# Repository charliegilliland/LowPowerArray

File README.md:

# LowPowerArray

This repository contains the hardware design files and firmware for a low-power acoustic array.
Up to 8 channels of microphone data are sampled at 48kHz and saved to an SD card.
Data acquisition is synchronized to UTC time with a GPS.

## Theory of Operation

### Power
The LowPowerArray can be powered via USB or pin headers on J101.
The power source is selected by placement of a jumper on J101.
A servo-style connector can be plugged into J101.
Refer to the schematics in [HardwareDesign](HardwareDesign/LowPowerArray/) for pin descriptions.

### Modes
There are two modes of operation: Manual and Automatic.
The mode is selected with a jumper on J201.

In Manual mode (jumper present) data acquisition is started and stopped using the pushbutton connected to J202.

In Automatic mode (jumper not present) data acquisition will begin automatically once power is applied and the GPS is locked.
If the button is pressed while in Automatic mode, the data acquisition will be stopped and the device will revert to Manual mode.

### Status
At startup, the device will wait for a GPS lock, unless ```GPS_WAIT_LOCK``` is defined as 0 (useful for lab testing).
When the GPS is locked, the LED will quickly illuminate several times, indicating that it is ready to start data acquisition.

While the data acquisition is running, the LED will illuminate every other second.

Status messages will be printed over the UART pins on J201, and also over USB via the virtual COM port.

### Programming
The STM32 microcontroller is programmed via SWD using the pins SWDIO, SWCLK, NRST on J201.
A Nucleo development board, or dedicated programmer, can be used to program the device.

### Microphone Connections
The 10-pin FFC connector, J1, is used to connect to a microphone board.

Alternatively, the BCLK, FSYNC, and DATA pins are available as pin headers on J201.

### SD Card Storage
Audio and GPS data are stored on the microSD card.
The card must be formatted as exFAT.

At startup, the device will create a new directory with the prefix ```filesXXXX```, where XXXX is a number: i.e. ```files0001```.

Audio and GPS files will be stored in the newly created directory, with file names ```audioXXXX.pcm``` and ```gpsXXXX.txt```.
Audio data is raw PCM format, with 8 channels and 32-bit word length.
GPS data is stored as plain text NMEA sentences, exactly as it is received from the GPS module.

GPS data can be tied to the audio data by matching the file numbers.
There is one pair of GPS messages for each second, where the first pair of GPS messages is tied to the first frame of audio in the audio file.

### GPS Module
The GPS module provides the PPS (pulse per second) and BCLK (bit clock) signals, as well as location and time via NMEA messages over UART.

Be sure to program the GPS module using the configuration file ```charlie-m8t-lowpower.txt```.

There is a battery connector, labeled BT101, which can provide backup power to the GPS.
The battery should be a 3v coin-cell or equivalent, and are commonly available as CMOS batteries.

Be sure to plug in the battery with the correct polarity (+ and - are marked on the v2 board).

If for some reason the GPS is not used, an auxiliary clock source can be used by populating a 12.288MHz crystal oscillator X501.
If this is used, select the clock source by placing R502 instead of R501.
Using the auxiliary clock source will require firmware changes to account for the missing PPS signal, and no GPS messages.
At time of writing this is not supported by the firmware.

For debugging purposes, when GPS lock is not required to start data acquisition, go to the file ```gps_mgr.h``` and change ```GPS_WAIT_LOCK``` to 0,
and re-program the device.
This will allow you to test the device in the lab, where GPS signals are not available.

## Programming Guide

### main.c
The file [main.c](Firmware/Core/Src/main.c) mostly contains code generated by CubeIDE. This file simply initializes the peripherals, and calls the user_app_init and user_app_loop functions.
This file should not have to be changed.

### user_app.c
The file [user_app.c](Firmware/Core/Src/user_app.c) contains the high-level runtime behavior of the device.
This includes the main endless while loop, the data acquisition loop, and button and PPS callback functions.

The endless while loop in user_app_loop implements the state diagram described below.

### aud_mgr.h
The file [aud_mgr.h](Firmware/Core/Inc/aud_mgr.h) contains the audio-specific code.
This uses the SAI peripheral in DMA mode, so that audio data can be received 'in the background' while the CPU is working on other tasks.

The ```HAL_SAI_RxCpltCallback``` is called by the hardware when a buffer of new data is ready.
In this function, the DMA buffer pointer is changed to the next buffer in the ring buffer.
The ring buffer allows for multiple buffers to be stored before they are written to the SD card. 

If there is an SAI error, or ring buffer overflow, the data acquisition will be stopped and the PPS will be re-synchronized.

### sd_mgr.h
The file [sd_mgr.h](Firmware/Core/Inc/sd_mgr.h) contains the sd card-specific code.
This code contains functions for starting new files, and writing to existing files.

### gps_mgr.h
The file [gps_mgr.h](Firmware/Core/Inc/gps_mgr.h) contains the GPS-specific code.
GPS data is received over USART2 in DMA mode.

When the GPS messages have been received, the ```HAL_UARTEx_RxEventCallback``` function will be called by the hardware.
The received messages will be copied to local buffers, and the RX will be restarted to handle the next message.

### inline functions
Many of the functions implemented in the peripheral files are ```inline``` functions.
This is done for execution speed: basically instead of actually calling those functions,
the compiler will copy that code to where the function was called.

### DAQ State Diagram
This figure describes the various states that the device can be in, and the events that cause a state change.
The ```daq_stat``` variable declared in user_app.c is used to read and change state in the code.

## Future Work

### Directory / file naming
It would probably be better to name the files using the UTC date and time as received from the GPS.
This would require parsing each GPS message, and some more logic for dealing with the timing in creating the files.

### Control and monitoring over UART / USB
It might be possible to start and stop the data acquisition over UART or USB, though I haven't explored this in detail.
This would allow a remote computer, such as a raspberry pi, to control the data acquisition.
Additionally, a telemetry radio could be connected to the UART serial port for remote status monitoring and control.

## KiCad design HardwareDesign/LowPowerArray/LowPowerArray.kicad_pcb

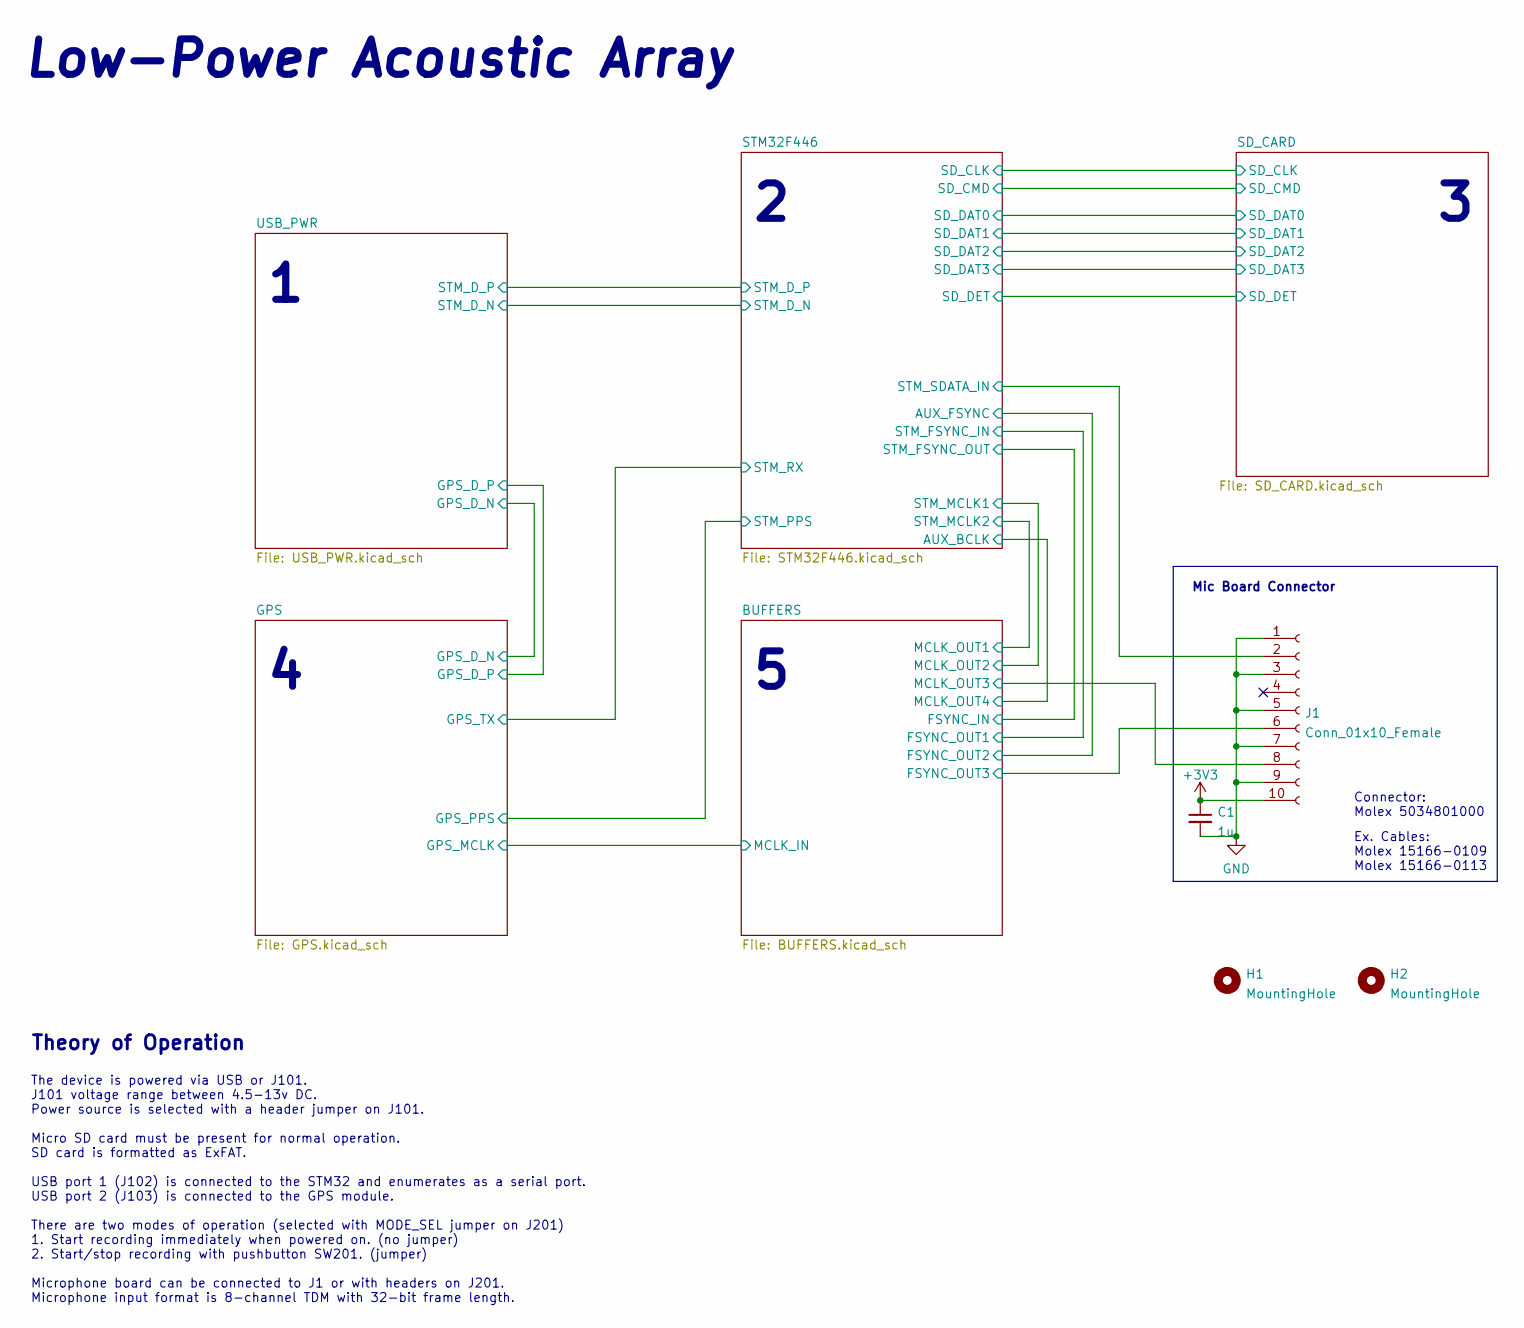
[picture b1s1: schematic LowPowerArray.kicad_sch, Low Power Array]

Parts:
C1: 1u; C_0402_1005Metric
H1, H2: MountingHole; MountingHole_3.2mm_M3
J1: Conn_01x10_Female; MOLEX_5034801000

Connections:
+3V3: C1.1, J1.10; also elsewhere on the board
/BUFFERS/FSYNC_OUT3: J1.6; also elsewhere on the board
/BUFFERS/MCLK_OUT3: J1.8; also elsewhere on the board
/STM32F446/STM_SDATA_IN: J1.2; also elsewhere on the board
GND: C1.2, J1.1, J1.3, J1.5, J1.7, J1.9; also elsewhere on the board

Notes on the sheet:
The device is powered via USB or J101. J101 voltage range between 4.5-13v DC. Power source is selected with a header jumper on J101. Micro SD card must be present for normal operation. SD card is formatted as ExFAT. USB port 1 (J102) is connected to the STM32 and enumerates as a serial port. USB po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
Connector: Molex 5034801000
Theory of Operation
Mic Board Connector
Low-Power Acoustic Array
Ex. Cables: Molex 15166-0109 Molex 15166-0113

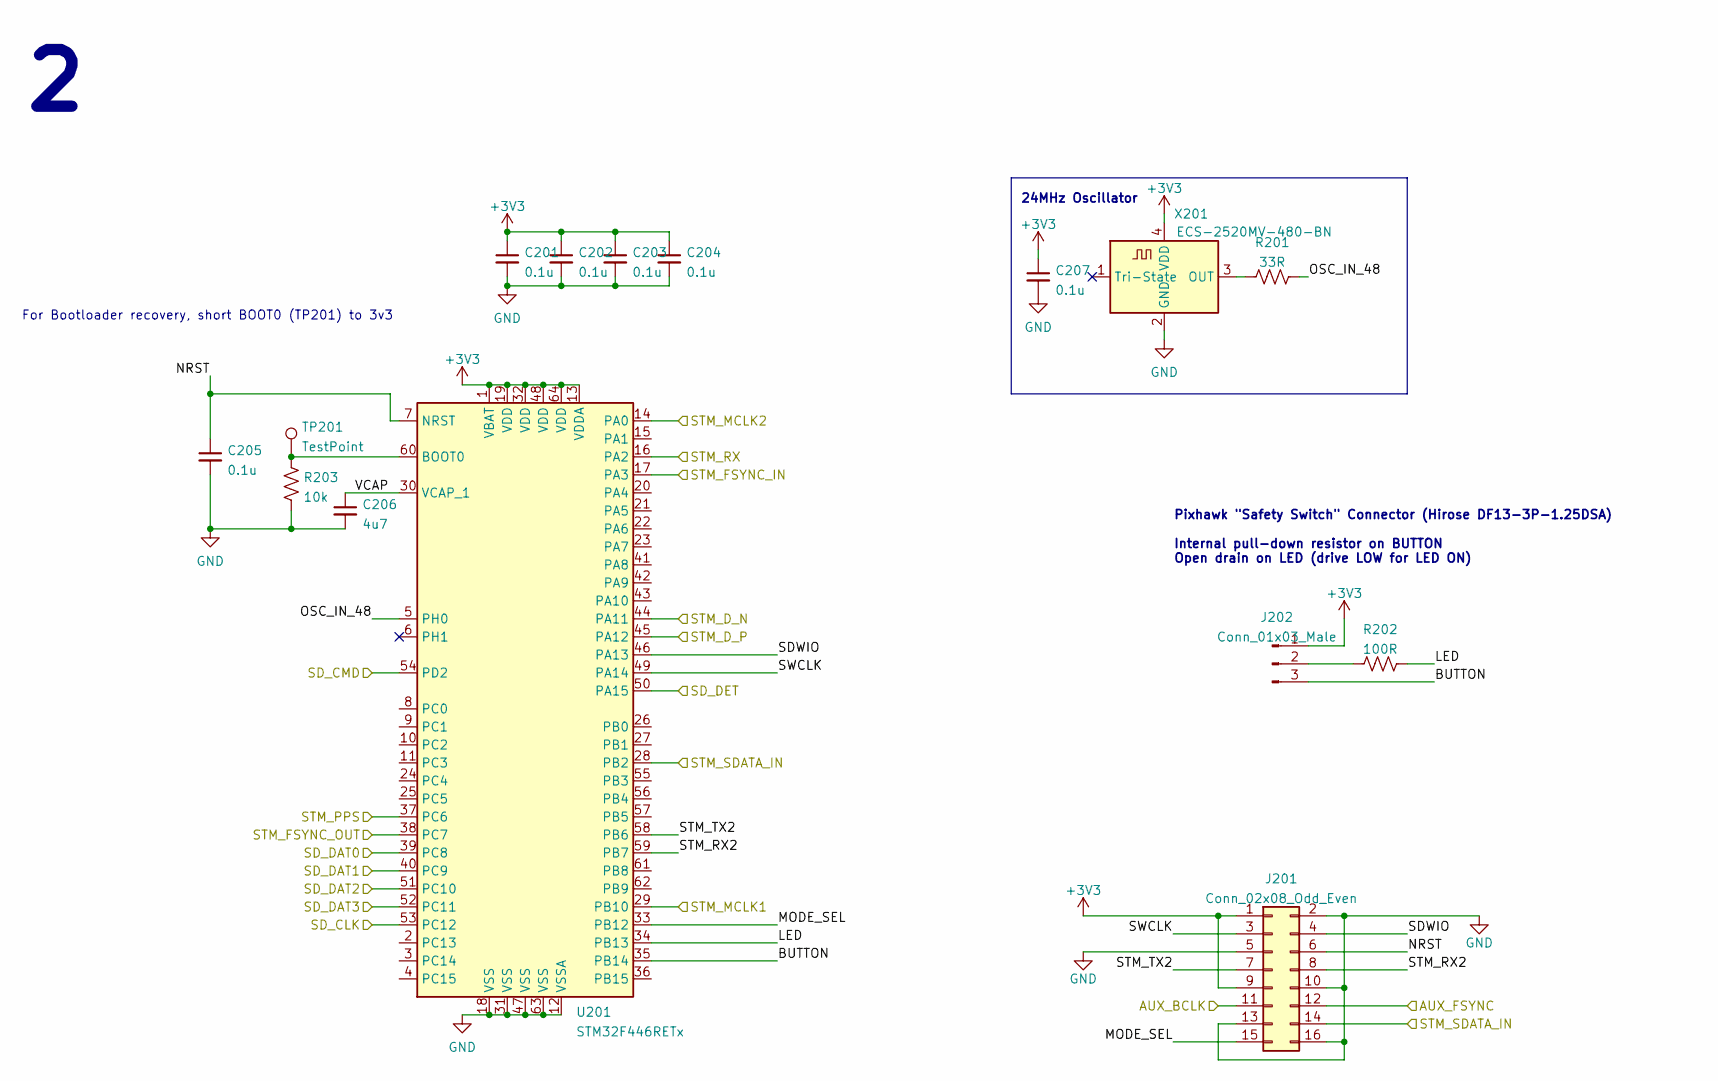
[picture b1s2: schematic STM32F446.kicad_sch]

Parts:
C201, C202, C203, C204, C205, C207: 0.1u; C_0402_1005Metric
C206: 4u7; C_0402_1005Metric
J201: Conn_02x08_Odd_Even; PinHeader_2x08_P2.54mm_Vertical_SMD
J202: Conn_01x03_Male; Hirose_DF13-03P-1.25DSA_1x03_P1.25mm_Vertical
R201: 33R; R_0402_1005Metric
R202: 100R; R_0402_1005Metric
R203: 10k; R_0402_1005Metric
TP201: TestPoint; TestPoint_Pad_D1.5mm
U201: STM32F446RETx; LQFP-64_10x10mm_P0.5mm
X201: ECS-2520MV-480-BN; Oscillator_SMD_ECS_2520MV-xxx-xx-4Pin_2.5x2.0mm

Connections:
+3V3: C201.1, C202.1, C203.1, C204.1, C207.1, J201.1, J201.9, J202.1, U201.1 (VBAT), U201.13 (VDDA), U201.19 (VDD), U201.32 (VDD), U201.48 (VDD), U201.64 (VDD), X201.4 (VDD); also elsewhere on the board
/BUFFERS/FSYNC_IN: U201.38 (PC7); also elsewhere on the board
/BUFFERS/FSYNC_OUT1: U201.17 (PA3); also elsewhere on the board
/BUFFERS/FSYNC_OUT2: J201.12; also elsewhere on the board
/BUFFERS/MCLK_OUT1: U201.14 (PA0); also elsewhere on the board
/BUFFERS/MCLK_OUT2: U201.29 (PB10); also elsewhere on the board
/BUFFERS/MCLK_OUT4: J201.11; also elsewhere on the board
/GPS/GPS_PPS: U201.37 (PC6); also elsewhere on the board
/GPS/GPS_TX: U201.16 (PA2); also elsewhere on the board
/SD_CARD/SD_CLK: U201.53 (PC12); also elsewhere on the board
/SD_CARD/SD_CMD: U201.54 (PD2); also elsewhere on the board
/SD_CARD/SD_DAT0: U201.39 (PC8); also elsewhere on the board
/SD_CARD/SD_DAT1: U201.40 (PC9); also elsewhere on the board
/SD_CARD/SD_DAT2: U201.51 (PC10); also elsewhere on the board
/SD_CARD/SD_DAT3: U201.52 (PC11); also elsewhere on the board
/SD_CARD/SD_DET: U201.50 (PA15); also elsewhere on the board
/STM32F446/BUTTON: J202.3, U201.35 (PB14)
/STM32F446/LED: R202.2, U201.34 (PB13)
/STM32F446/MODE_SEL: J201.15, U201.33 (PB12)
/STM32F446/NRST: C205.1, J201.6, U201.7 (NRST)
/STM32F446/OSC_IN_48: R201.2, U201.5 (PH0)
/STM32F446/SDWIO: J201.4, U201.46 (PA13)
/STM32F446/STM_D_N: U201.44 (PA11); also elsewhere on the board
/STM32F446/STM_D_P: U201.45 (PA12); also elsewhere on the board
/STM32F446/STM_RX2: J201.8, U201.59 (PB7)
/STM32F446/STM_SDATA_IN: J201.14, U201.28 (PB2); also elsewhere on the board
/STM32F446/STM_TX2: J201.7, U201.58 (PB6)
/STM32F446/SWCLK: J201.3, U201.49 (PA14)
/STM32F446/VCAP: C206.1, U201.30 (VCAP_1)
GND: C201.2, C202.2, C203.2, C204.2, C205.2, C206.2, C207.2, J201.2, J201.5, J201.10, J201.13, J201.16, R203.1, U201.12 (VSSA), U201.18 (VSS), U201.31 (VSS), U201.47 (VSS), U201.63 (VSS), X201.2 (GND); also elsewhere on the board
unnamed: J202.2, R202.1
unnamed: R201.1, X201.3 (OUT)
unnamed: R203.2, TP201.1, U201.60 (BOOT0)

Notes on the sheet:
24MHz Oscillator
For Bootloader recovery, short BOOT0 (TP201) to 3v3
Pixhawk "Safety Switch" Connector (Hirose DF13-3P-1.25DSA) Internal pull-down resistor on BUTTON Open drain on LED (drive LOW for LED ON)

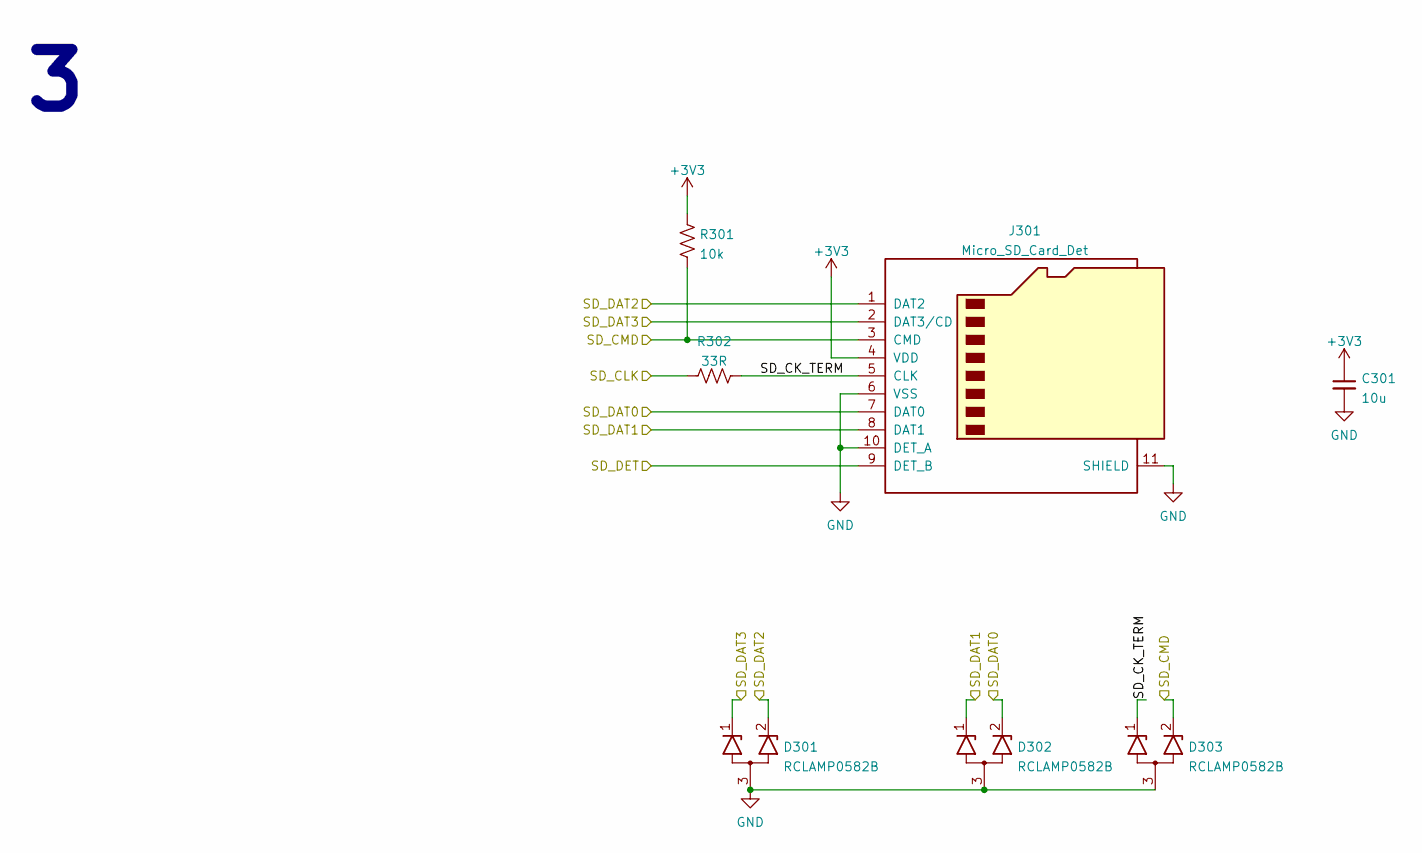
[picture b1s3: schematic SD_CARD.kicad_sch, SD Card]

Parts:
C301: 10u; C_0805_2012Metric
D301, D302, D303: RCLAMP0582B; SOT-416
J301: Micro_SD_Card_Det; microSD_HC_Molex_104031-0811
R301: 10k; R_0402_1005Metric
R302: 33R; R_0402_1005Metric

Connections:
+3V3: C301.1, J301.4 (VDD), R301.1; also elsewhere on the board
/SD_CARD/SD_CK_TERM: D303.1 (K1), J301.5 (CLK), R302.2
/SD_CARD/SD_CLK: R302.1; also elsewhere on the board
/SD_CARD/SD_CMD: D303.2 (K2), J301.3 (CMD), R301.2; also elsewhere on the board
/SD_CARD/SD_DAT0: D302.2 (K2), J301.7 (DAT0); also elsewhere on the board
/SD_CARD/SD_DAT1: D302.1 (K1), J301.8 (DAT1); also elsewhere on the board
/SD_CARD/SD_DAT2: D301.2 (K2), J301.1 (DAT2); also elsewhere on the board
/SD_CARD/SD_DAT3: D301.1 (K1), J301.2 (DAT3/CD); also elsewhere on the board
/SD_CARD/SD_DET: J301.9 (DET_B); also elsewhere on the board
GND: C301.2, D301.3 (A), D302.3 (A), D303.3 (A), J301.6 (VSS), J301.10 (DET_A), J301.11 (SHIELD); also elsewhere on the board

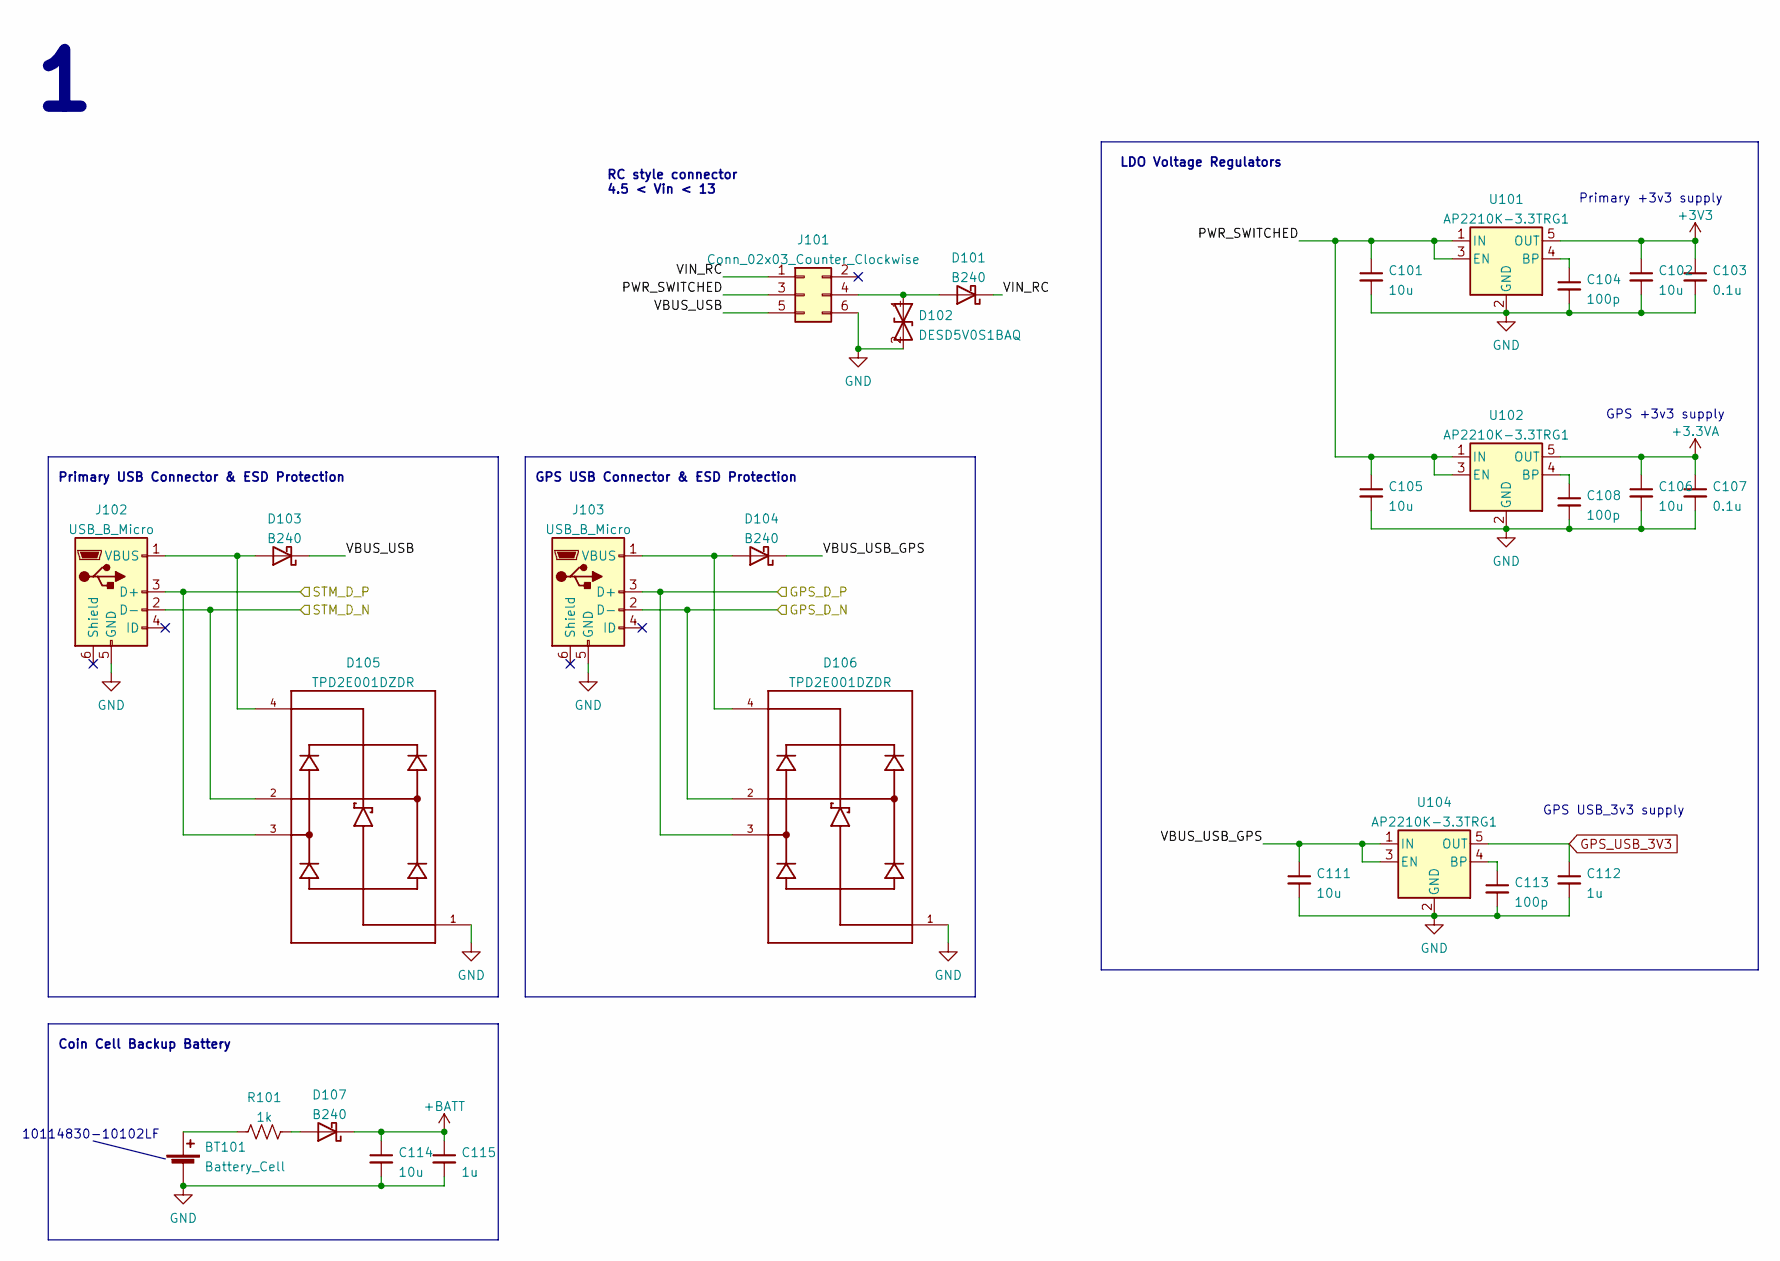
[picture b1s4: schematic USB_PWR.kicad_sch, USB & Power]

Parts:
BT101: Battery_Cell; Amphenol_10114830-10102LF
C101, C102, C105, C106, C111, C114: 10u; C_0805_2012Metric
C103, C107: 0.1u; C_0402_1005Metric
C104, C108, C113: 100p; C_0402_1005Metric
C112, C115: 1u; C_0402_1005Metric
D101, D103, D104, D107: B240; D_SMB
D102: DESD5V0S1BAQ; D_SOD-323
D105, D106: TPD2E001DZDR; SOT192P237X122-4N; PARTREV I
J101: Conn_02x03_Counter_Clockwise; PinHeader_2x03_P2.54mm_Vertical
J102, J103: USB_B_Micro; USB_Micro-B_Molex_47346-0001
R101: 1k; R_0402_1005Metric
U101, U102, U104: AP2210K-3.3TRG1; SOT-23-5

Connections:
+3.3VA: C106.1, C107.1, U102.5 (OUT); also elsewhere on the board
+3V3: C102.1, C103.1, U101.5 (OUT); also elsewhere on the board
+BATT: C114.1, C115.1, D107.1 (K); also elsewhere on the board
/GPS/GPS_D_N: D106.2, J103.2 (D-); also elsewhere on the board
/GPS/GPS_D_P: D106.3, J103.3 (D+); also elsewhere on the board
/STM32F446/STM_D_N: D105.2, J102.2 (D-); also elsewhere on the board
/STM32F446/STM_D_P: D105.3, J102.3 (D+); also elsewhere on the board
/USB_PWR/PWR_SWITCHED: C101.1, C105.1, J101.3, U101.1 (IN), U101.3 (EN), U102.1 (IN), U102.3 (EN)
/USB_PWR/VBUS_USB: D103.1 (K), J101.5
/USB_PWR/VBUS_USB_GPS: C111.1, D104.1 (K), U104.1 (IN), U104.3 (EN)
/USB_PWR/VIN_RC: D101.1 (K), J101.1
GND: BT101.2 (-), C101.2, C102.2, C103.2, C104.2, C105.2, C106.2, C107.2, C108.2, C111.2, C112.2, C113.2, C114.2, C115.2, D102.2 (A2), D105.1, D106.1, J101.6, J102.5 (GND), J103.5 (GND), U101.2 (GND), U102.2 (GND), U104.2 (GND); also elsewhere on the board
GPS_USB_3V3: C112.1, U104.5 (OUT); also elsewhere on the board
unnamed: BT101.1 (+), R101.1
unnamed: C104.1, U101.4 (BP)
unnamed: C108.1, U102.4 (BP)
unnamed: C113.1, U104.4 (BP)
unnamed: D101.2 (A), D102.1 (A1), J101.4
unnamed: D103.2 (A), D105.4, J102.1 (VBUS)
unnamed: D104.2 (A), D106.4, J103.1 (VBUS)
unnamed: D107.2 (A), R101.2

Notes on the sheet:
GPS USB Connector & ESD Protection
RC style connector 4.5 < Vin < 13
GPS +3v3 supply
Coin Cell Backup Battery
GPS USB_3v3 supply
Primary USB Connector & ESD Protection
LDO Voltage Regulators
Primary +3v3 supply
10114830-10102LF

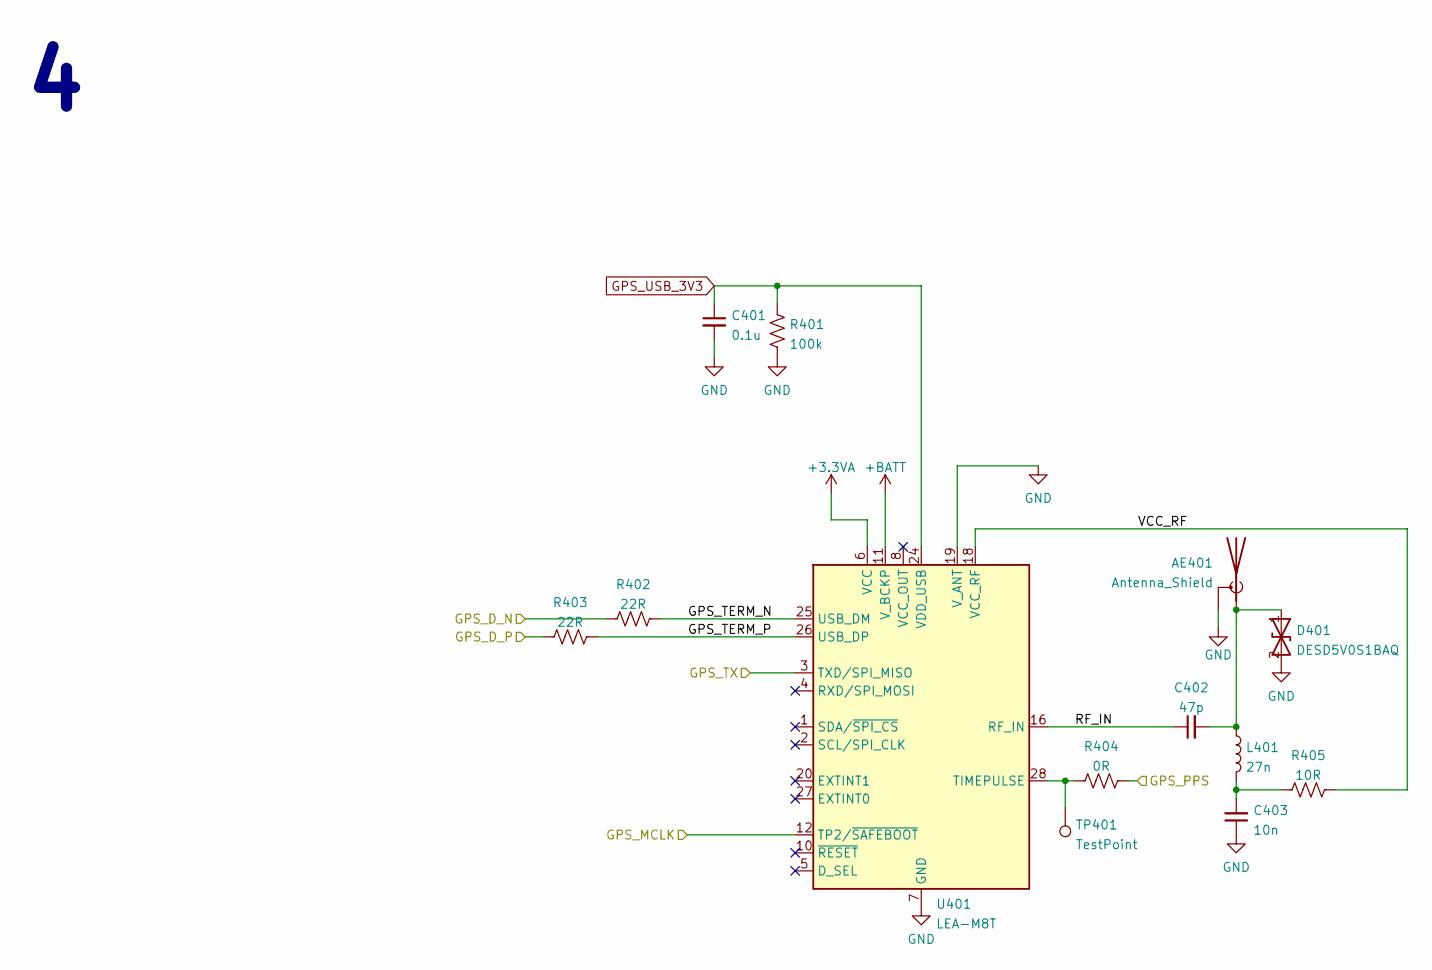
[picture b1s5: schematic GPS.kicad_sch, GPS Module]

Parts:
AE401: Antenna_Shield; U.FL_Hirose_U.FL-R-SMT-1_Vertical
C401: 0.1u; C_0402_1005Metric
C402: 47p; C_0402_1005Metric
C403: 10n; C_0402_1005Metric
D401: DESD5V0S1BAQ; D_SOD-323
L401: 27n; L_0402_1005Metric
R401: 100k; R_0402_1005Metric
R402, R403: 22R; R_0402_1005Metric
R404: 0R; R_0402_1005Metric
R405: 10R; R_0402_1005Metric
TP401: TestPoint; TestPoint_Pad_D1.5mm
U401: LEA-M8T; ublox_LEA

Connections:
+3.3VA: U401.6 (VCC); also elsewhere on the board
+BATT: U401.11 (V_BCKP); also elsewhere on the board
/BUFFERS/MCLK_IN: U401.12 (TP2/~SAFEBOOT); also elsewhere on the board
/GPS/GPS_D_N: R402.1; also elsewhere on the board
/GPS/GPS_D_P: R403.1; also elsewhere on the board
/GPS/GPS_PPS: R404.2; also elsewhere on the board
/GPS/GPS_TERM_N: R402.2, U401.25 (USB_DM)
/GPS/GPS_TERM_P: R403.2, U401.26 (USB_DP)
/GPS/GPS_TX: U401.3 (TXD/SPI_MISO); also elsewhere on the board
/GPS/RF_IN: C402.1, U401.16 (RF_IN)
/GPS/VCC_RF: R405.2, U401.18 (VCC_RF)
GND: AE401.2 (Shield), C401.2, C403.1, D401.2 (A2), R401.1, U401.7 (GND), U401.13 (GND), U401.14 (GND), U401.15 (GND), U401.17 (GND), U401.19 (V_ANT); also elsewhere on the board
GPS_USB_3V3: C401.1, R401.2, U401.24 (VDD_USB); also elsewhere on the board
unnamed: AE401.1 (A), C402.2, D401.1 (A1), L401.1
unnamed: C403.2, L401.2, R405.1
unnamed: R404.1, TP401.1, U401.28 (TIMEPULSE)

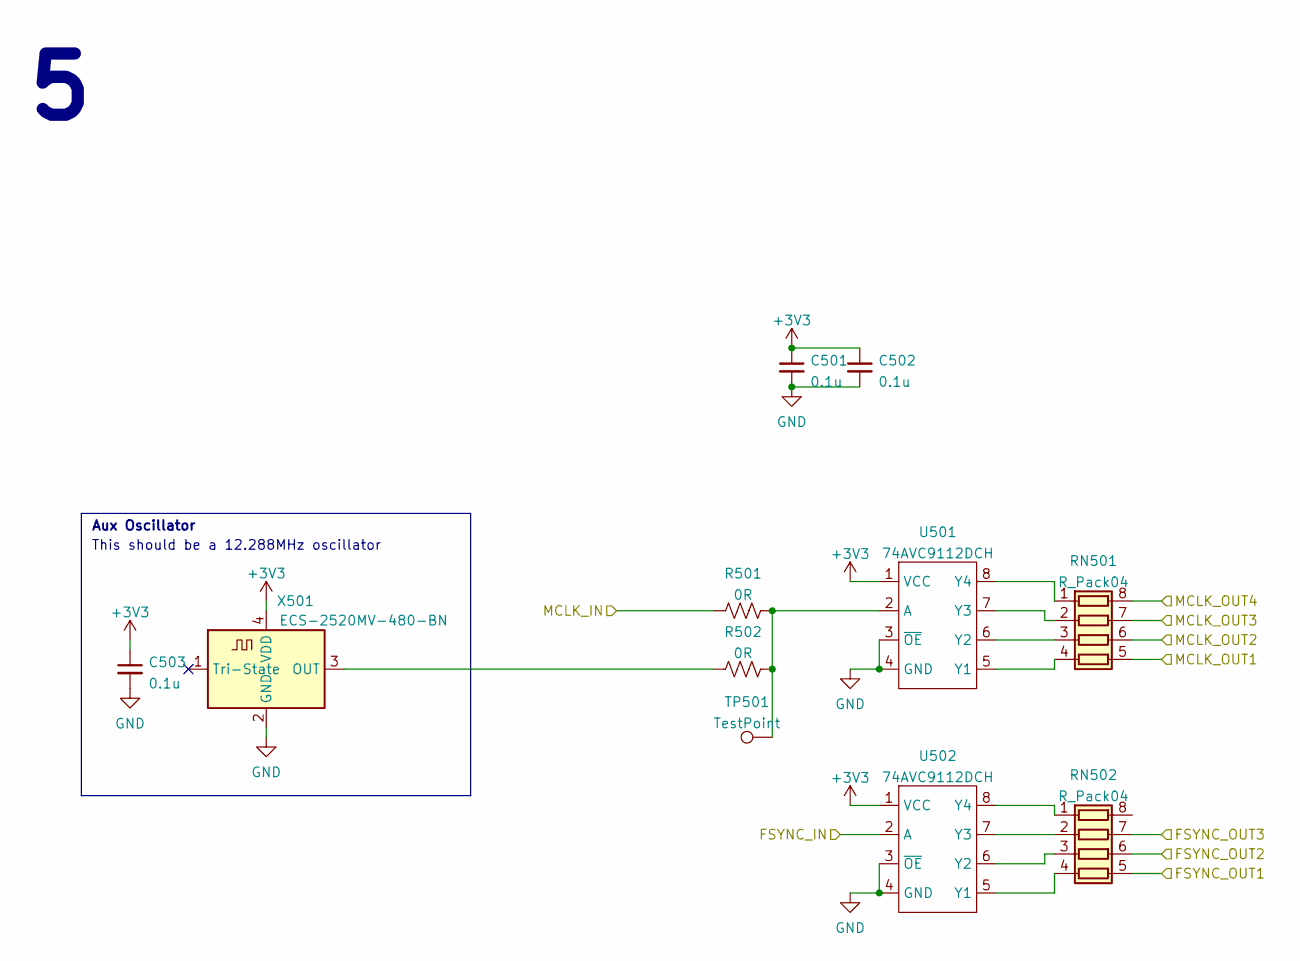
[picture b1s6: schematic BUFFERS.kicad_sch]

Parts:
C501, C502, C503: 0.1u; C_0402_1005Metric
R501, R502: 0R; R_0402_1005Metric
RN501, RN502: R_Pack04; R_Array_Concave_4x0402
TP501: TestPoint; TestPoint_Pad_D1.5mm
U501, U502: 74AVC9112DCH; VSSOP-8_2.3x2mm_P0.5mm
X501: ECS-2520MV-480-BN; Oscillator_SMD_ECS_2520MV-xxx-xx-4Pin_2.5x2.0mm

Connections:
+3V3: C501.1, C502.1, C503.1, U501.1 (VCC), U502.1 (VCC), X501.4 (VDD); also elsewhere on the board
/BUFFERS/FSYNC_IN: U502.2 (A); also elsewhere on the board
/BUFFERS/FSYNC_OUT1: RN502.5 (R4.2); also elsewhere on the board
/BUFFERS/FSYNC_OUT2: RN502.6 (R3.2); also elsewhere on the board
/BUFFERS/FSYNC_OUT3: RN502.7 (R2.2); also elsewhere on the board
/BUFFERS/MCLK_IN: R501.1; also elsewhere on the board
/BUFFERS/MCLK_OUT1: RN501.5 (R4.2); also elsewhere on the board
/BUFFERS/MCLK_OUT2: RN501.6 (R3.2); also elsewhere on the board
/BUFFERS/MCLK_OUT3: RN501.7 (R2.2); also elsewhere on the board
/BUFFERS/MCLK_OUT4: RN501.8 (R1.2); also elsewhere on the board
GND: C501.2, C502.2, C503.2, U501.3 (~OE), U501.4 (GND), U502.3 (~OE), U502.4 (GND), X501.2 (GND); also elsewhere on the board
unnamed: R501.2, R502.2, TP501.1, U501.2 (A)
unnamed: R502.1, X501.3 (OUT)
unnamed: RN501.1 (R1.1), U501.8 (Y4)
unnamed: RN501.2 (R2.1), U501.7 (Y3)
unnamed: RN501.3 (R3.1), U501.6 (Y2)
unnamed: RN501.4 (R4.1), U501.5 (Y1)
unnamed: RN502.1 (R1.1), U502.8 (Y4)
unnamed: RN502.2 (R2.1), U502.7 (Y3)
unnamed: RN502.3 (R3.1), U502.6 (Y2)
unnamed: RN502.4 (R4.1), U502.5 (Y1)

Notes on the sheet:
This should be a 12.288MHz oscillator
Aux Oscillator

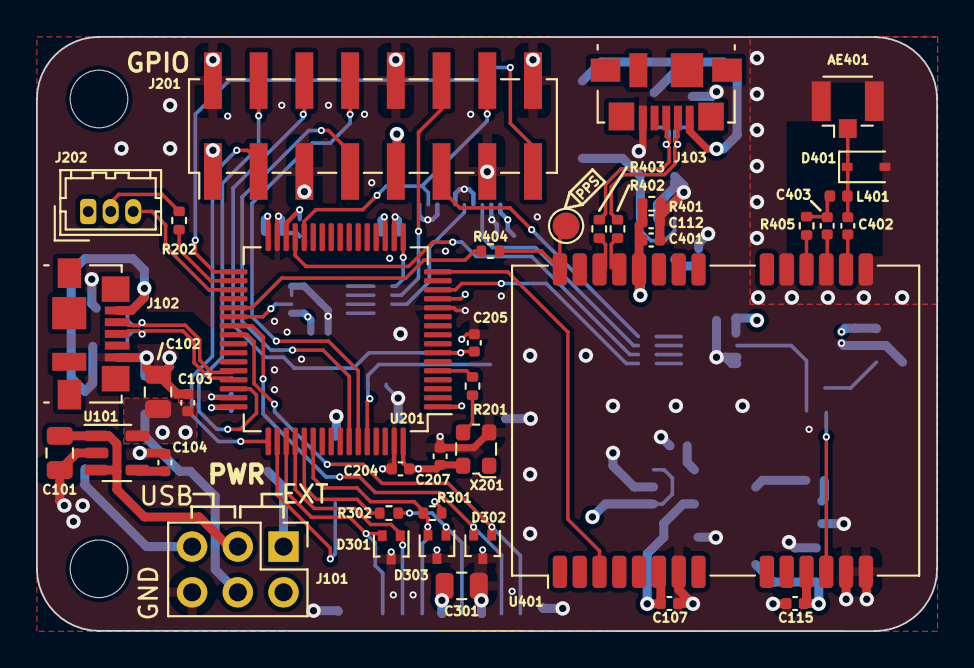
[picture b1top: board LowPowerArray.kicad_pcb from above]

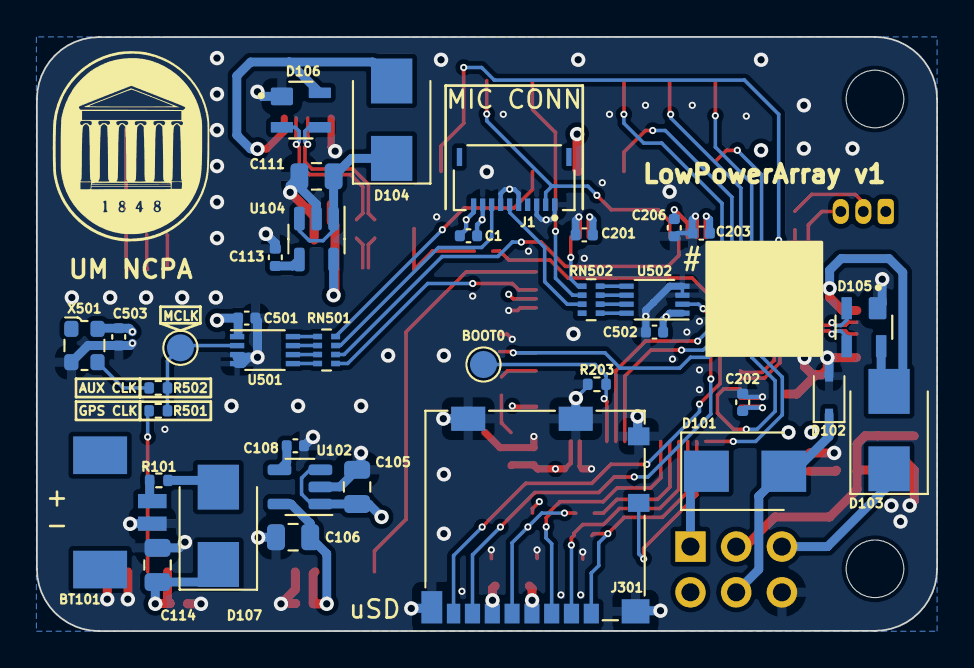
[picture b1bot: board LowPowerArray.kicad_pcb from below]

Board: 6 copper layers, 50.0 x 33.0 mm, 78 parts (37 on the bottom side), 71 nets.

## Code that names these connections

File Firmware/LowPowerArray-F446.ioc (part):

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Mcu.Name=STM32F446R(C-E)Tx
Mcu.Package=LQFP64
Mcu.UserName=STM32F446RETx
PA0-WKUP.Signal=S_TIM8_ETR
PA11.Mode=Device_Only
PA11.Signal=USB_OTG_FS_DM
PA12.Mode=Device_Only
PA12.Signal=USB_OTG_FS_DP
PA13.Mode=Serial_Wire
PA13.Signal=SYS_JTMS-SWDIO
PA14.Mode=Serial_Wire
PA14.Signal=SYS_JTCK-SWCLK
PA15.GPIOParameters=GPIO_PuPd,GPIO_Label
PA15.GPIO_Label=SD_DETECT
PA15.GPIO_PuPd=GPIO_PULLUP
PA15.Signal=GPIO_Input
PA2.Mode=Half_duplex(single_wire_mode)
PA2.Signal=USART2_TX
PA3.Mode=SAI_A_AsyncSlave
PA3.Signal=SAI1_FS_A
PB10.Mode=SAI_A_AsyncSlave
PB10.Signal=SAI1_SCK_A
PB12.GPIOParameters=GPIO_PuPd,GPIO_Label
PB12.GPIO_Label=MODE_SEL
PB12.GPIO_PuPd=GPIO_PULLUP
PB12.Signal=GPIO_Input
PB13.GPIOParameters=PinState,GPIO_PuPd,GPIO_Label,GPIO_ModeDefaultOutputPP
PB13.GPIO_Label=USER_LED
PB13.GPIO_ModeDefaultOutputPP=GPIO_MODE_OUTPUT_OD
PB13.GPIO_PuPd=GPIO_NOPULL
PB13.PinState=GPIO_PIN_RESET
PB13.Signal=GPIO_Output
PB14.GPIOParameters=GPIO_PuPd,GPIO_Label
PB14.GPIO_Label=USER_BTN
PB14.GPIO_PuPd=GPIO_PULLDOWN
PB14.Signal=GPXTI14
PB2.GPIOParameters=GPIO_PuPd
PB2.GPIO_PuPd=GPIO_NOPULL
PB2.Mode=SAI_A_AsyncSlave
PB2.Signal=SAI1_SD_A
PB6.Mode=Asynchronous
PB6.Signal=USART1_TX
PB7.Mode=Asynchronous
PB7.Signal=USART1_RX
PC10.GPIOParameters=GPIO_PuPd
PC10.GPIO_PuPd=GPIO_PULLUP
PC10.Mode=SD_4_bits_Wide_bus
PC10.Signal=SDIO_D2
PC11.GPIOParameters=GPIO_PuPd
PC11.GPIO_PuPd=GPIO_PULLUP
PC11.Mode=SD_4_bits_Wide_bus
PC11.Signal=SDIO_D3
PC12.Mode=SD_4_bits_Wide_bus
PC12.Signal=SDIO_CK
PC6.GPIOParameters=GPIO_Label,GPIO_ModeDefaultEXTI
PC6.GPIO_Label=PPS_INPUT
PC6.GPIO_ModeDefaultEXTI=GPIO_MODE_IT_FALLING
PC6.Signal=S_TIM8_CH1
PC7.GPIOParameters=GPIO_Speed,GPIO_Label
PC7.GPIO_Label=TIM_FSYNC_OUT
PC7.GPIO_Speed=GPIO_SPEED_FREQ_VERY_HIGH
PC7.Signal=S_TIM8_CH2
PC8.GPIOParameters=GPIO_PuPd
PC8.GPIO_PuPd=GPIO_PULLUP
PC8.Mode=SD_4_bits_Wide_bus
PC8.Signal=SDIO_D0
PC9.GPIOParameters=GPIO_PuPd
PC9.GPIO_PuPd=GPIO_PULLUP
PC9.Mode=SD_4_bits_Wide_bus
PC9.Signal=SDIO_D1
PD2.Mode=SD_4_bits_Wide_bus
PD2.Signal=SDIO_CMD
PH0-OSC_IN.Mode=HSE-External-Clock-Source
PH0-OSC_IN.Signal=RCC_OSC_IN
PH1-OSC_OUT.Mode=HSE-External-Clock-Source
PH1-OSC_OUT.Signal=RCC_OSC_OUT
RCC.HSE_VALUE=24000000
RCC.SYSCLKFreq_VALUE=168000000
RCC.SYSCLKSource=RCC_SYSCLKSOURCE_PLLCLK
board=custom

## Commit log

2023-11-22 Add README.md
